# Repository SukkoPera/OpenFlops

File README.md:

# OpenFlops
OpenFlops is an Open Hardware Floppy Disk Drive emulator/simulator.

### Summary
From [Wikipedia](https://en.wikipedia.org/wiki/Floppy_disk_hardware_emulator):
> Older models of computers, electronic keyboards and industrial automation often used floppy disk drives for data transfer. Older equipment may be difficult to replace or upgrade because of cost, requirement for continuous availability or unavailable upgrades. Proper operation may require operating system, software and data to be read and written from and to floppies, forcing users to maintain floppy drives on supporting systems.

> Floppy disks and floppy drives are gradually going out of production, and replacement of malfunctioning drives, and the systems hosting them, is becoming increasingly difficult. Floppy disks themselves are fragile, or may need to be replaced often. An alternative is to use a floppy disk hardware emulator, a device which appears to be a standard floppy drive to the old equipment by interfacing directly to the floppy disk controller, while storing data in another medium such as a USB thumb drive, Secure Digital card, or a shared drive on a computer network. Emulators can also be used as a higher-performance replacement for mechanical floppy disk drives. 

OpenFlops is an Open Hardware implementation of such an emulator, inspired from the ubiquitous Gotek hardware. It is designed to run the [FlashFloppy](https://github.com/keirf/FlashFloppy) firmware, which gives it several improvements over the original Gotek:
- Can be installed on [many different platforms](https://github.com/keirf/FlashFloppy/wiki/Host-Platforms)
- Directly supports a [wide range of image formats](https://github.com/keirf/FlashFloppy/wiki/Image-Formats)
- [Flexible track layout](https://github.com/keirf/FlashFloppy/wiki/Track-Layouts) for Raw Sector Images
- [Extremely configurable](https://github.com/keirf/FlashFloppy/wiki/FF.CFG-Configuration-File)
- Supports [AutoSwap](https://github.com/keirf/FF_AutoSwap) for games with a large number of disks
- Easily accessible pin headers for connection of a [i2c display](https://github.com/keirf/FlashFloppy/wiki/Hardware-Mods#lcd-display) (either OLED or LCD), [rotary encoder](https://github.com/keirf/FlashFloppy/wiki/Hardware-Mods#rotary-encoder) (including power)
- Built-in amplified speaker, or easily-accessible pin header for an external one
- USB connector can either be soldered on the board or connected to a pin header
- Connected Motor signal
- Emulates two drives at the same time (Not yet supported by the firmware, but [it will come](https://github.com/keirf/FlashFloppy/wiki/Donations))
- Has additional 3.3V, 5V and GND power pins
- And hey, it's Open Hardware!

All of this comes in the same form factor (and mounting holes) as the board installed in the original Gotek, hence it can be easily installed in any shell or enclosure designed for it.

### Assembly and Installation
Solder all components to the board. I suggest starting with the main microcontroller (U3), as it uses an LQFP package which is tricky to solder: the recommended technique is drag soldering, there are many videos about that on YouTube, so please look there for advice. I recommend soldering the bare minimum components needed for programming and then trying to flash it right away. This way you will be able to fix your soldering without too many components getting in the way, if needed. You will need a USB/TTL Serial converter for this: one with 3.3V I/O level is recommended, but a 5V one can be used, too (most pins on STM32 microcontrollers are 5V-tolerant, so don't worry, it's not a bad hack!). You shouldn't pay more than 1-2€ for it in any case, anyway. So, when you are ready:

- Solder U3, Y1, C3 and C5, then the programming header (the top one with power, BOOT0, TX, RX, etc.)
- Check for shorts on the 3.3V power lines, you can easily do this on the pads for C6-C10
- If your USB/Serial adapter has a 3.3V output, connect it to 3.3V on the power header, then connect ground, RX and TX
- If no 3.3V output is available, solder U4 and power the board through the 5V pin on the power header

Now you should be able to [program the STM32 microcontroller](https://github.com/keirf/FlashFloppy/wiki/Firmware-Programming). If you have difficultes you can try adding R10 (and C4) and maybe a few of C6-C10, but most likely the problem will be with the solder joints on U3, as soldering this kind of package manually is never easy, so please get a lens (or even better, a microscope) and double-check your job.

The serial adapter is only necessary for the first flashing. Subsequent updates [can be done easily via USB](https://github.com/keirf/FlashFloppy/wiki/Firmware-Update).

Note that most components are necessary, but there are a few you can skip if you are feeling lazy:
- If you are not interested in the head movement sound, you can skip the following components: SPK1, D2, R5, R6, Q7.
- If your LCD/OLED display already has pull-up resistors for the SDA/SCK lines (most do), you can skip R3 and R4.

### Configuration
Please refer to the FlashFloppy wiki for the [initial setup](https://github.com/keirf/FlashFloppy/wiki/Initial-Setup) and an overview of the [available configuration options](https://github.com/keirf/FlashFloppy/wiki/FF.CFG-Configuration-File).

Some options that you will want to override the default values of, in order to take advantage of all the features OpenFlops provides, are the following:
- `motor-delay`
- `rotary`
- `display-type`

### Releases
If you want to get this board produced, you are recommended to get [the latest release](https://github.com/SukkoPera/OpenFlops/releases) rather than the current git version, as the latter might be under development and is not guaranteed to be working.

Every release is accompanied by its Bill Of Materials (BOM) file and any relevant notes about it, which you are recommended to read carefully.

### License
The OpenFlops documentation, including the design itself, is copyright &copy; SukkoPera 2019-2020.

OpenFlops is Open Hardware licensed under the [CERN OHL v. 1.2](http://ohwr.org/cernohl).

You may redistribute and modify this documentation under the terms of the CERN OHL v.1.2. This documentation is distributed *as is* and WITHOUT ANY EXPRESS OR IMPLIED WARRANTIES whatsoever with respect to its functionality, operability or use, including, without limitation, any implied warranties OF MERCHANTABILITY, SATISFACTORY QUALITY, FITNESS FOR A PARTICULAR PURPOSE or infringement. We expressly disclaim any liability whatsoever for any direct, indirect, consequential, incidental or special damages, including, without limitation, lost revenues, lost profits, losses resulting from business interruption or loss of data, regardless of the form of action or legal theory under which the liability may be asserted, even if advised of the possibility or likelihood of such damages.

A copy of the full license is included in file [LICENSE.pdf](LICENSE.pdf), please refer to it for applicable conditions. In order to properly deal with its terms, please see file [LICENSE_HOWTO.pdf](LICENSE_HOWTO.pdf).

The contact points for information about manufactured Products (see section 4.2) are listed in file [PRODUCT.md](PRODUCT.md).

Any modifications made by Licensees (see section 3.4.b) shall be recorded in file [CHANGES.md](CHANGES.md).

The Documentation Location of the original project is https://github.com/SukkoPera/OpenFlops/.

### Support the Project
Since the project is open you are free to get the PCBs made by your preferred manufacturer, however in case you want to support the development, you can order them from PCBWay through this link:

You get my gratitude and cheap, professionally-made and good quality PCBs, I get some credit that will help with this and [other projects](https://www.pcbway.com/project/member/shareproject/?bmbid=41100). You won't even have to worry about the various PCB options, it's all pre-configured for you!

Also, if you still have to register to that site, [you can use this link](https://www.pcbway.com/setinvite.aspx?inviteid=41100) to get some bonus initial credit (and yield me some more).

Again, if you want to use another manufacturer, feel free to, don't feel obligated :). But then you can buy me a coffee if you want:

### Thanks
- H.M for publishing the [original Gotek schematics](doc/gotek_usb-fde_block-diagram.jpg)
- [keirf](https://github.com/keirf) for FlashFloppy
- Brian Allan for suggesting some improvements for the Speaker circuit
- Ray Bellis for suggesting adding pin headers for the USB port and speaker
- Mario Babeu for suggesting to line up the orientation of LD1 and LD2
- Patrick Kerkhof for sending me a lot of original Gotek housing for dimensional testing

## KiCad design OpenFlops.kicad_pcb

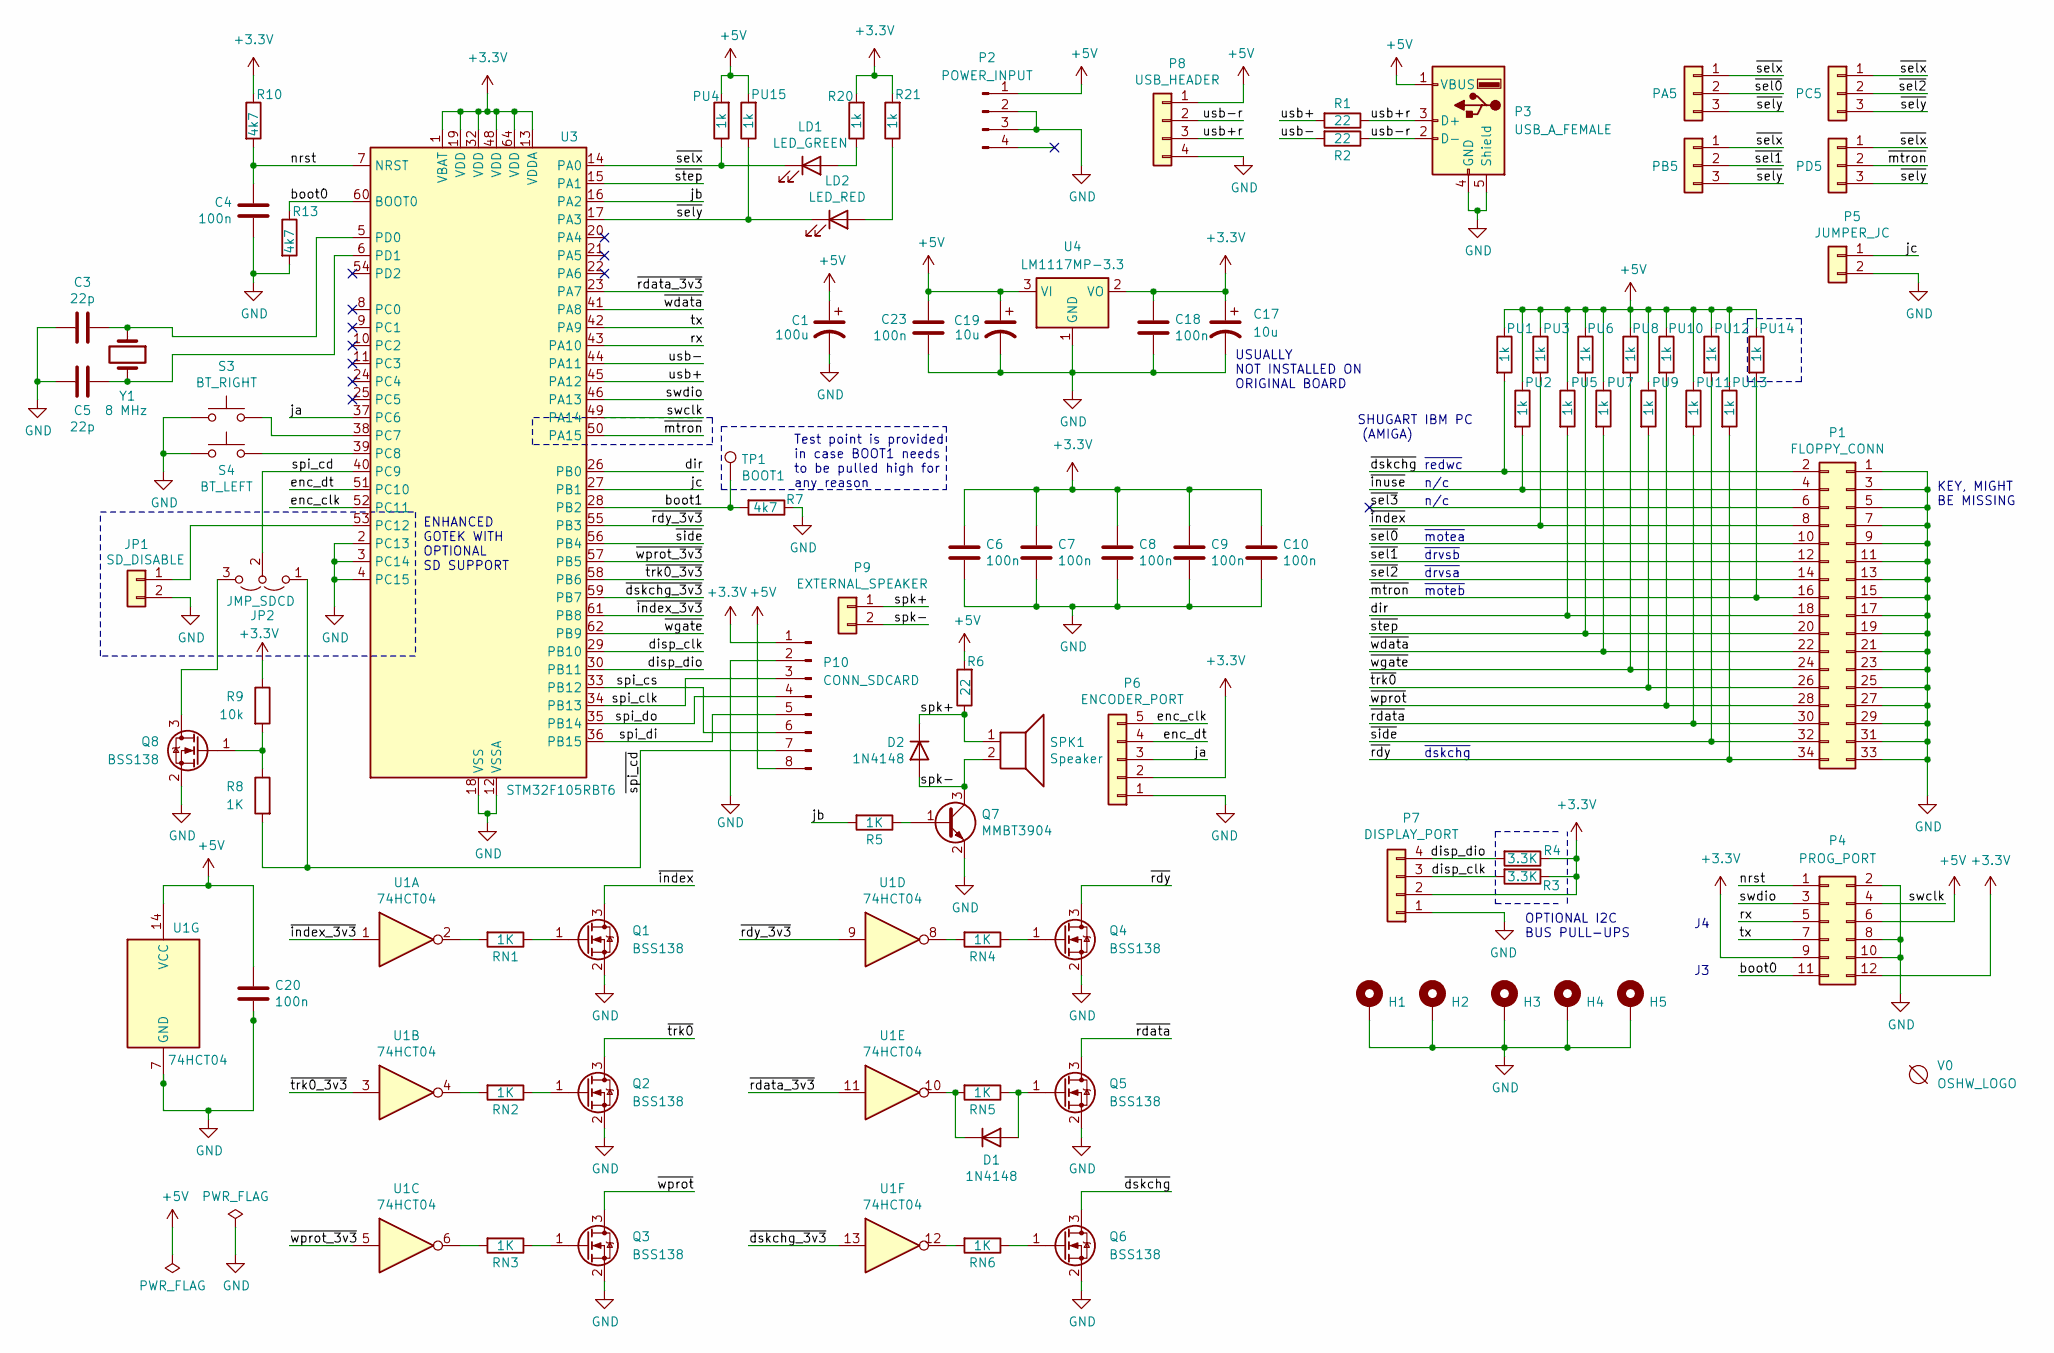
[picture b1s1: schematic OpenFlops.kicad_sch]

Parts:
C1: 100u; CP_Elec_5x5.8; MFG Part Num UCD0J101MCL6GS; JLCPCB PN C445483
C3, C5: 22p; C_0805_2012Metric_Pad1.18x1.45mm_HandSolder; MFG Part Num CL21C220JBANNNC; JLCPCB PN C1804
C4, C6, C7, C8, C9, C10, C18, C20, C23: 100n; C_0805_2012Metric_Pad1.18x1.45mm_HandSolder; MFG Part Num CC0805KRX7R9BB104; JLCPCB PN C49678
C17, C19: 10u; CP_Elec_5x5.8; MFG Part Num UCD1H100MCL6GS; JLCPCB PN C445463
D1, D2: 1N4148; D_SOD-323_HandSoldering; MFG Part Num 1N4148WS; JLCPCB PN C2128
H1, H2, H3, H4, H5: MountingHole_Pad; MountingHole_M3_Pad
JP1: SD_DISABLE; PinHeader_1x02_P2.54mm_Vertical
JP2: JMP_SDCD; SolderJumper-3_P1.3mm_Open_RoundedPad1.0x1.5mm
LD1: LED_GREEN; LED_D3.0mm
LD2: LED_RED; LED_D3.0mm
P1: FLOPPY_CONN; PinHeader_2x17_P2.54mm_Vertical
P2: POWER_INPUT; PinHeader_1x04_P2.54mm_Vertical
P3: USB_A_FEMALE
P4: PROG_PORT; PinHeader_2x06_P2.54mm_Vertical
P5: JUMPER_JC; PinHeader_1x02_P2.54mm_Vertical
P6: ENCODER_PORT; PinHeader_1x05_P2.54mm_Vertical
P7: DISPLAY_PORT; PinHeader_1x04_P2.54mm_Vertical
P8: USB_HEADER; PinHeader_1x04_P2.54mm_Vertical
P9: EXTERNAL_SPEAKER; PinHeader_1x02_P2.54mm_Mute
P10: CONN_SDCARD; PinHeader_1x08_P2.54mm_Vertical
PA5: Conn_01x03; PinHeader_1x03_P2.54mm_Mute
PB5: Conn_01x03; PinHeader_1x03_P2.54mm_Mute
PC5: Conn_01x03; PinHeader_1x03_P2.54mm_Mute
PD5: Conn_01x03; PinHeader_1x03_P2.54mm_Mute
PU1, PU2, PU3, PU4, PU5, PU6, PU7, PU8, PU9, PU10, PU11, PU12, PU13, PU14, PU15: 1k; R_0805_2012Metric_Pad1.20x1.40mm_HandSolder; MFG Part Num 0805W8F1001T5E; JLCPCB PN C17513
Q1, Q2, Q3, Q4, Q5, Q6, Q8: BSS138; SOT-23_Handsolder; MFG Part Num BSS138; JLCPCB PN C7420339
Q7: MMBT3904; SOT-23_Handsolder; MFG Part Num MMBT3904(RANGE:100-300); JLCPCB PN C20526
R1, R2, R6: 22; R_0805_2012Metric_Pad1.20x1.40mm_HandSolder; MFG Part Num 0805W8F220JT5E; JLCPCB PN C17561
R3, R4: 3.3K; R_0805_2012Metric_Pad1.20x1.40mm_HandSolder; MFG Part Num 0805W8F3301T5E; JLCPCB PN C26010
R5, R8: 1K; R_0805_2012Metric_Pad1.20x1.40mm_HandSolder; MFG Part Num 0805W8F1001T5E; JLCPCB PN C17513
R7, R10, R13: 4k7; R_0805_2012Metric_Pad1.20x1.40mm_HandSolder; MFG Part Num 0805W8F4701T5E; JLCPCB PN C17673
R9: 10k; R_0805_2012Metric_Pad1.20x1.40mm_HandSolder; MFG Part Num 0805W8F1001T5E; JLCPCB PN C17513
R20, R21: 1k; R_0805_2012Metric_Pad1.20x1.40mm_HandSolder; MFG Part Num 0805W8F1001T5E; JLCPCB PN C17513
RN1, RN2, RN3, RN4, RN5, RN6: 1K; R_0805_2012Metric_Pad1.20x1.40mm_HandSolder; MFG Part Num 0805W8F1001T5E; JLCPCB PN C17513
S3: BT_RIGHT; PUSH_BUTTON_RIGHT_ANGLE
S4: BT_LEFT; PUSH_BUTTON_RIGHT_ANGLE
SPK1: Speaker; Buzzer
TP1: BOOT1; TestPoint_Pad_D1.0mm
U1: 74HCT04; SOIC-14_3.9x8.7mm_P1.27mm; MFG Part Num 74HC04D,653; JLCPCB PN C5590
U3: STM32F105RBT6; LQFP-64_10x10mm_P0.5mm; MFG Part Num AT32F435RGT7; JLCPCB PN C3029577
U4: LM1117MP-3.3; SOT-223-3_TabPin2; MFG Part Num AMS1117-3.3; JLCPCB PN C6186
V0: OSHW_LOGO; OSHW-Logo2_7.3x6mm_Copper
Y1: 8 MHz; Crystal_SMD_HC49-SD; MFG Part Num X49SM8MSD2SC; JLCPCB PN C12674

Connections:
+3.3V: C6.1, C7.1, C8.1, C9.1, C10.1, C17.1, C18.1, P4.9, P4.12, P6.2, P7.2, P10.1, R3.1, R4.1, R9.1, R10.1, R20.2, R21.2, U3.1 (VBAT), U3.13 (VDDA), U3.19 (VDD), U3.32 (VDD), U3.48 (VDD), U3.64 (VDD), U4.2 (VO)
+5V: C1.1, C19.1, C20.1, C23.1, P2.1, P3.1 (VBUS), P4.6, P8.1, P10.8, PU1.1, PU2.1, PU3.1, PU4.2, PU5.1, PU6.1, PU7.1, PU8.1, PU9.1, PU10.1, PU11.1, PU12.1, PU13.1, PU14.1, PU15.2, R6.2, U1.14 (VCC), U4.3 (VI)
/boot0: P4.11, R13.1, U3.60 (BOOT0)
/boot1: R7.2, TP1.1, U3.28 (PB2)
/dir: P1.18, PU5.2, U3.26 (PB0)
/disp_clk: P7.3, R3.2, U3.29 (PB10)
/disp_dio: P7.4, R4.2, U3.30 (PB11)
/enc_clk: P6.5, U3.52 (PC11)
/enc_dt: P6.4, U3.51 (PC10)
/ja: P6.3, U3.37 (PC6)
/jb: R5.2, U3.16 (PA2)
/jc: P5.1, U3.27 (PB1)
/nrst: C4.1, P4.1, R10.2, U3.7 (NRST)
/rx: P4.5, U3.43 (PA10)
/spi_cd: JP2.2 (C), U3.40 (PC9)
/spi_clk: P10.3, U3.34 (PB13)
/spi_cs: P10.6, U3.33 (PB12)
/spi_di: P10.5, U3.36 (PB15)
/spi_do: P10.4, U3.35 (PB14)
/spk+: D2.1 (K), P9.1, R6.1, SPK1.1
/spk-: D2.2 (A), P9.2, Q7.3 (C), SPK1.2
/swclk: P4.4, U3.49 (PA14)
/swdio: P4.3, U3.46 (PA13)
/tx: P4.7, U3.42 (PA9)
/usb+: R1.2, U3.45 (PA12)
/usb+r: P3.3 (D+), P8.3, R1.1
/usb-: R2.2, U3.44 (PA11)
/usb-r: P3.2 (D-), P8.2, R2.1
/~dskchg_3v3: U1.13, U3.59 (PB7)
/~dskchg: P1.2, PU1.2, Q6.3 (D)
/~index_3v3: U1.1, U3.61 (PB8)
/~index: P1.8, PU3.2, Q1.3 (D)
/~inuse: P1.4, PU2.2
/~mtron: P1.16, PD5.2, PU14.2, U3.50 (PA15)
/~rdata_3v3: U1.11, U3.23 (PA7)
/~rdata: P1.30, PU11.2, Q5.3 (D)
/~rdy_3v3: U1.9, U3.55 (PB3)
/~rdy: P1.34, PU13.2, Q4.3 (D)
/~sel0: P1.10, PA5.2
/~sel1: P1.12, PB5.2
/~sel2: P1.14, PC5.2
/~sel3: P1.6
/~selx: LD1.1 (K), PA5.1, PB5.1, PC5.1, PD5.1, PU4.1, U3.14 (PA0)
/~sely: LD2.1 (K), PA5.3, PB5.3, PC5.3, PD5.3, PU15.1, U3.17 (PA3)
/~side: P1.32, PU12.2, U3.56 (PB4)
/~spi_cd: JP2.1 (A), P10.7, R8.2
/~step: P1.20, PU6.2, U3.15 (PA1)
/~trk0_3v3: U1.3, U3.58 (PB6)
/~trk0: P1.26, PU9.2, Q2.3 (D)
/~wdata: P1.22, PU7.2, U3.41 (PA8)
/~wgate: P1.24, PU8.2, U3.62 (PB9)
/~wprot_3v3: U1.5, U3.57 (PB5)
/~wprot: P1.28, PU10.2, Q3.3 (D)
GND: C1.2, C3.2, C4.2, C5.2, C6.2, C7.2, C8.2, C9.2, C10.2, C17.2, C18.2, C19.2, C20.2, C23.2, H1.1, H2.1, H3.1, H4.1, H5.1, JP1.2, P1.1, P1.3, P1.5, P1.7, P1.9, P1.11, P1.13, P1.15, P1.17, P1.19, P1.21, P1.23, P1.25, P1.27, P1.29, P1.31, P1.33, P2.2, P2.3, P3.4 (GND), P3.5 (Shield), P4.2, P4.8, P4.10, P5.2, P6.1, P7.1, P8.4, P10.2, Q1.2 (S), Q2.2 (S), Q3.2 (S), Q4.2 (S), Q5.2 (S), Q6.2 (S), Q7.2 (E), Q8.2 (S), R7.1, R13.2, S3.2, S4.1, U1.7 (GND), U3.2 (PC13), U3.3 (PC14), U3.4 (PC15), U3.12 (VSSA), U3.18 (VSS), U3.31 (VSS), U3.47 (VSS), U3.63 (VSS), U4.1 (GND)
unnamed: D1.2 (A), Q5.1 (G), RN5.1
unnamed: D1.1 (K), RN5.2, U1.10
unnamed: JP1.1, U3.53 (PC12)
unnamed: JP2.3 (B), Q8.3 (D)
unnamed: LD1.2 (A), R20.1
unnamed: LD2.2 (A), R21.1
unnamed: Q1.1 (G), RN1.1
unnamed: Q2.1 (G), RN2.1
unnamed: Q3.1 (G), RN3.1
unnamed: Q4.1 (G), RN4.1
unnamed: Q6.1 (G), RN6.1
unnamed: Q7.1 (B), R5.1
unnamed: Q8.1 (G), R8.1, R9.2
unnamed: RN1.2, U1.2
unnamed: RN2.2, U1.4
unnamed: RN3.2, U1.6
unnamed: RN4.2, U1.8
unnamed: RN6.2, U1.12
unnamed: S3.1, U3.38 (PC7)
unnamed: S4.2, U3.39 (PC8)
unnamed: C3.1, U3.5 (PD0), Y1.1
unnamed: C5.1, U3.6 (PD1), Y1.2

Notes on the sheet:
OPTIONAL I2C BUS PULL-UPS
~{moteb}
ENHANCED GOTEK WITH OPTIONAL SD SUPPORT
n/c
KEY, MIGHT BE MISSING
~{drvsb}
IBM PC
Test point is provided in case BOOT1 needs to be pulled high for any reason
USUALLY NOT INSTALLED ON ORIGINAL BOARD
~{motea}
~{redwc}
~{dskchg}
SHUGART (AMIGA)
~{drvsa}

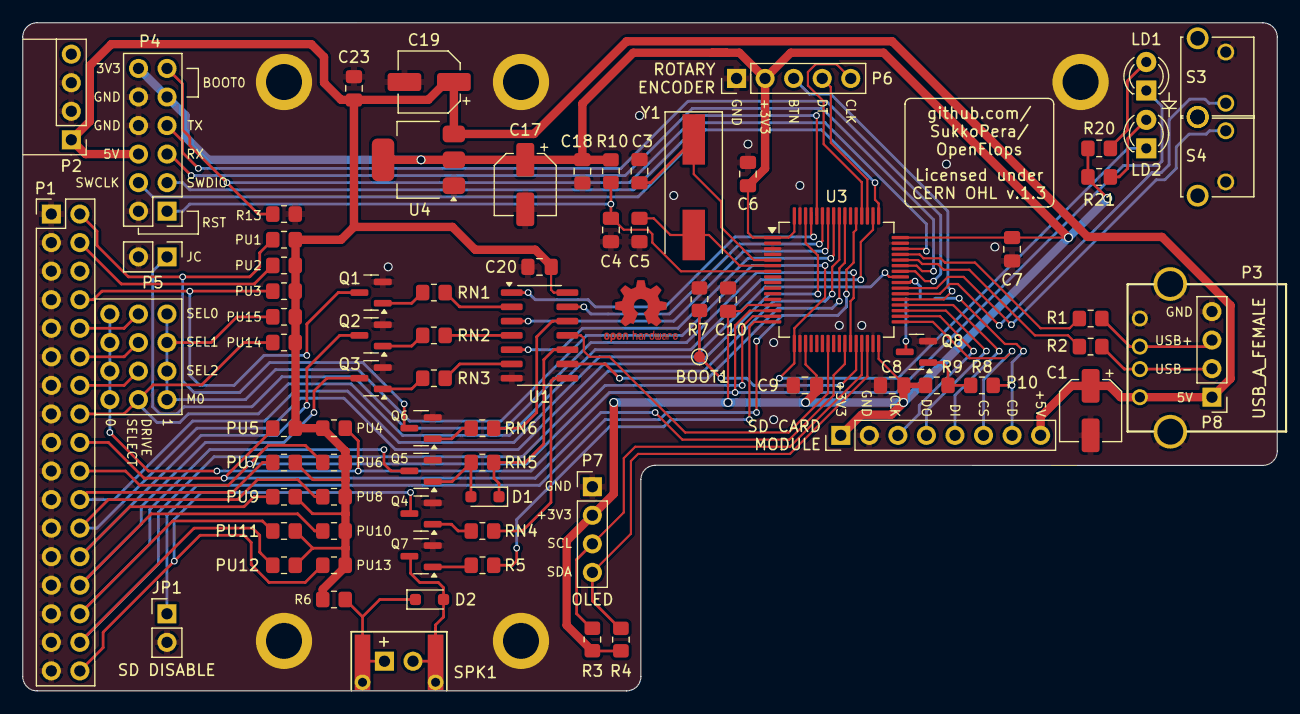
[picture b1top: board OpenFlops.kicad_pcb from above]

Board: 2 copper layers, 111.6 x 59.4 mm, 90 parts (1 on the bottom side), 75 nets.

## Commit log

2019-07-25 Fix PU3
2019-07-25 Fix JB/JC
2019-07-27 And we're done! This is a first rev of the PCB, done "by eye" as similarly as possible as one of my boards. There are quite a few improvements that we can make...
2019-07-27 Add mounting holes and several refinements
2019-07-27 Fix labels
2019-07-28 Improve power distribution
2019-07-28 Put power connectors on spare P4 pins
2019-07-28 Fix track width
2019-08-04 Make this an enhanced drive for FlashFloppy
2019-08-04 Add current-limiting resistor on speaker
2019-08-04 Add protection diode on speaker. Thanks Brian Allan
2019-08-04 Update PCB
2019-08-04 Add renders
2019-08-04 Improve ground plane
2019-08-04 Add P6/P7 pin names
2019-08-04 74HC04 -> 74HCT04
2019-08-04 Some refinements
2019-08-14 Rework power tracks, depolarize OLED/encoder connectors
2019-08-14 Use SOT-23 footprints for MOSFETs
2019-08-18 Use SOD-323 footprint for diodes
2019-08-18 Minor silkscreen adjustments
2019-08-18 Use same orientation for LD1 and LD2 - Thanks Mario Babeu
2019-08-18 Fix LD2 silkscreen position and add LED install legend
2019-08-18 Better position LED legend
2019-08-18 Add header for USB and speaker signals - Thanks Ray Bellis
2019-08-21 Lotsa cosmetic fixes
2019-08-21 Make LQFP-64 footprint easier to handsolder
2019-08-21 Ready for V1!
2019-10-09 Fix #2
2019-10-09 Fix #3
2019-10-09 Fix #4
2019-10-09 Make R6 22R
2019-10-09 Fix dimension
2019-10-09 Some more ground stitching
2019-10-09 Add BOOT1 testpoint and lots of changes for auto P&P
2019-11-19 Typos
2020-01-01 Final touches for V1final
2020-01-01 Move renders to img/
2020-01-01 Fixes for BOM
2020-01-01 Add note about release notes
2020-01-02 Add missing license files
2020-01-02 Add thanks
2020-01-02 Fix link
2023-02-06 Refine design
2024-08-15 Merge SD card changes from @COREi64; update to KiCad v8
    This includes https://github.com/SukkoPera/OpenFlops/pull/18 from @COREi64 and updates the file formats to KiCad v8
2024-08-15 Change C1, C17 and C19 to SMD parts
    This commit changes C1, C17 and C19 to SMD electrolytic capacitors. The Panasonic FT series (see https://industrial.panasonic.com/cdbs/www-data/pdf/RDE0000/ABA0000C1240.pdf) has both 10µF and 100µF a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
2024-08-16 Major rerouting Still not completely satisfied though
2024-08-16 Update footprints
2024-08-16 Move license/URL to front
2024-08-16 Update MCU footprint MCU and MOSFET are no longer "handsolder", not sure if it's OK...
2024-08-18 Switch crystal to SMD
2024-08-18 Update jlcpcb part numbers
2024-08-23 Final touches
2024-08-23 Add +5V to SD module connector
2024-08-23 Move BOOT1 and improve ground under MCU
2024-09-17 Add inversion circuit for SD detect signal
2024-10-23 Make MOSFETs slightly more handsolder-friendly and move Q8 down a bit
2026-02-13 Change Ko-fi image link in README
    Updated the Ko-fi link image in the README.
2026-02-13 Remove 'Get Help' section from README
    Removed the 'Get Help' section from the README.

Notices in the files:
OpenFlops.kicad_pcb:
Licensed under CERN OHL v.1.2
CERN OHL v.1.3
OpenFlops.kicad_sch:
Licensed under CERN OHL v.1.3
